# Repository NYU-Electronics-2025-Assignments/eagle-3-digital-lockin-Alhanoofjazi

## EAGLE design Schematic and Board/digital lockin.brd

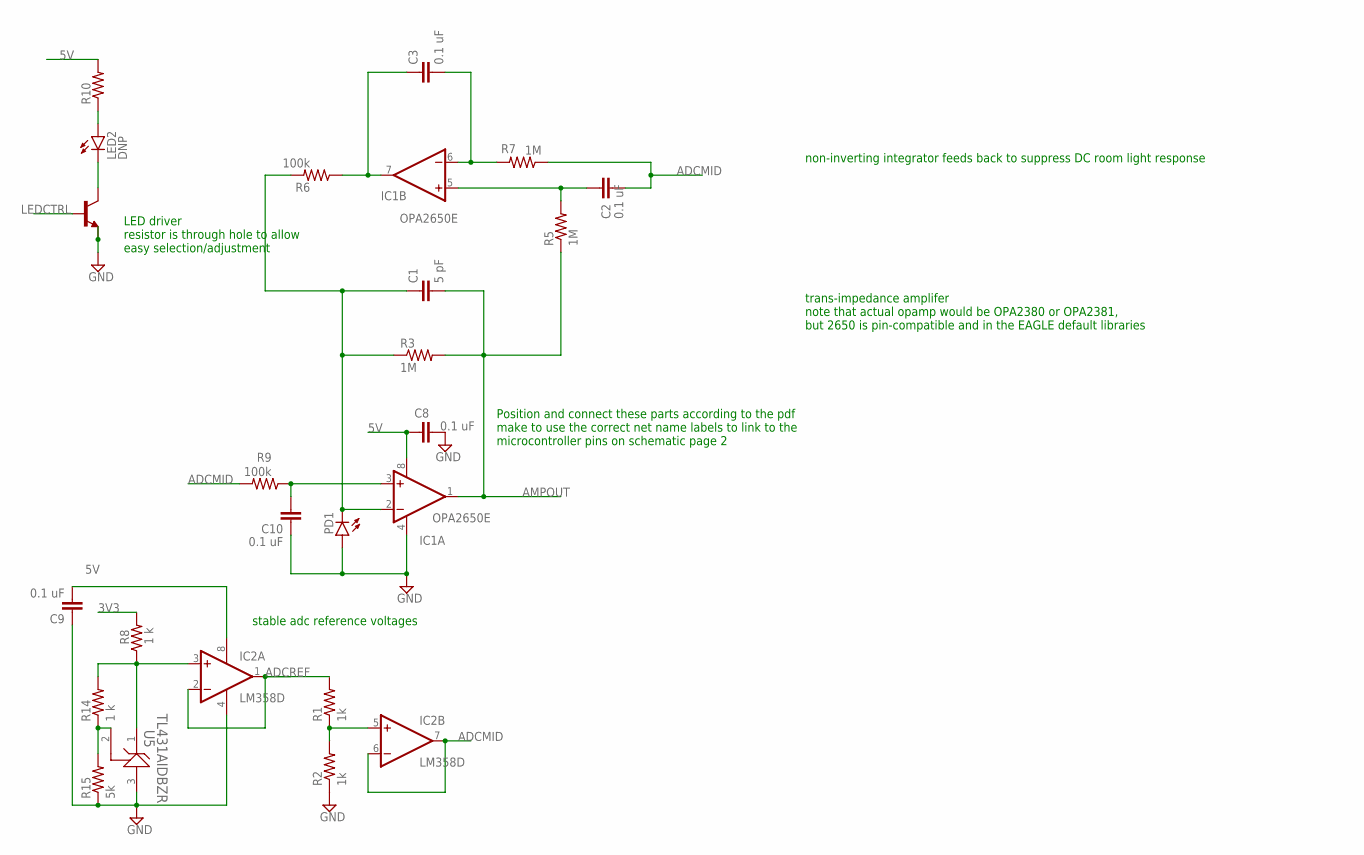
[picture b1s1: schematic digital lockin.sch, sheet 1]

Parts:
C1: 5 pF; C0805
C2, C3, C8, C9, C10: 0.1 uF; C0805; LCSC_PART# C28233
IC1: OPA2650E; MSOP08; LCSC_PART# C181662
IC2: LM358D; SO08; LCSC_PART# C7950
LED2: DNP; LED5MM
PD1: DNP; LED5MM
R1, R2: 1k; R0805; LCSC_PART# C17513
R3, R5, R7: 1M; R0805; LCSC_PART# C17514
R6, R9: 100k; R0805; LCSC_PART# C149504
R8, R14: 1 k; R0805; LCSC_PART# C17513
R10: DNP; 0204V
R15: 5k; R0805
T2: NPN; SOT23-BEC; LCSC_PART# C2145
U5: TL431AIDBZR; DBZ0003A_N; LCSC_PART# C3113

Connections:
3V3: R8.2; also elsewhere on the board
5V: C9.2, IC2.8 (V+), R10.2; also elsewhere on the board
ADCMID: IC2.6 (-IN), IC2.7 (OUT); also elsewhere on the board
ADCREF: IC2.1 (OUT), IC2.2 (-IN), R1.2; also elsewhere on the board
GND: C8.2, C9.1, C10.1, IC1.4 (V-), IC2.4 (V-), PD1.A, R2.1, R15.1, T2.E, U5.3 (ANODE); also elsewhere on the board
LEDCTRL: T2.B; also elsewhere on the board
unnamed: C2.1, IC1.5 (+IN), R5.2
unnamed: C1.1, IC1.2 (-IN), PD1.K (C), R3.1, R6.2
unnamed: LED2.K (C), T2.C
unnamed: C2.2, R7.1
unnamed: C3.2, IC1.6 (-IN), R7.2
unnamed: C3.1, IC1.7 (OUT), R6.1
unnamed: C1.2, IC1.1 (OUT), R3.2, R5.1
unnamed: C8.1, IC1.8 (V+)
unnamed: IC2.3 (+IN), R8.1, R14.2, U5.1 (CATHODE)
unnamed: IC2.5 (+IN), R1.1, R2.2
unnamed: LED2.A, R10.1
unnamed: C10.2, IC1.3 (+IN), R9.1
unnamed: R14.1, R15.2, U5.2 (REF)

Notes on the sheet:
non-inverting integrator feeds back to suppress DC room light response
trans-impedance amplifer note that actual opamp would be OPA2380 or OPA2381, but 2650 is pin-compatible and in the EAGLE default libraries
LED driver resistor is through hole to allow easy selection/adjustment
stable adc reference voltages
Position and connect these parts according to the pdf make to use the correct net name labels to link to the microcontroller pins on schematic page 2
ADCMID
AMPOUT

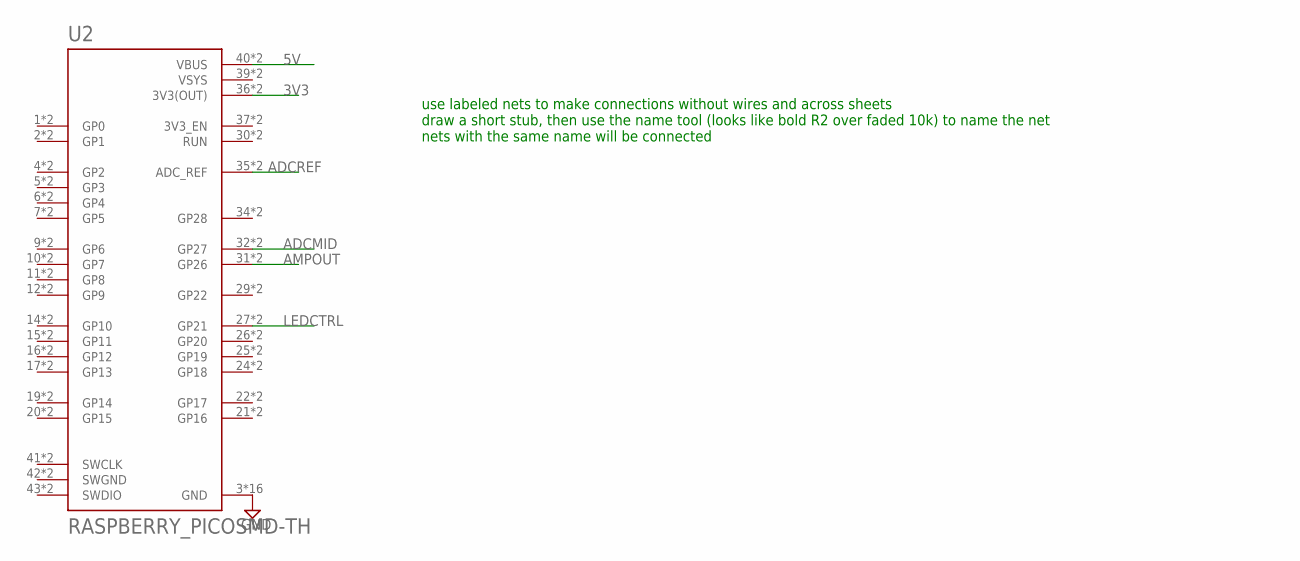
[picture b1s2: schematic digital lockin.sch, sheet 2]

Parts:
U2: RASPBERRY_PICOSMD-TH; PICO-PKG

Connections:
3V3: U2.36 (3V3(OUT)), U2.P$36 (3V3(OUT)); also elsewhere on the board
5V: U2.40 (VBUS), U2.P$40 (VBUS); also elsewhere on the board
ADCMID: U2.32 (GP27), U2.P$32 (GP27); also elsewhere on the board
ADCREF: U2.35 (ADC_REF), U2.P$35 (ADC_REF); also elsewhere on the board
AMPOUT: U2.31 (GP26), U2.P$31 (GP26)
GND: U2.3 (GND), U2.8 (GND), U2.13 (GND), U2.18 (GND), U2.23 (GND), U2.28 (GND), U2.33 (GND), U2.38 (GND), U2.P$3 (GND), U2.P$8 (GND), U2.P$13 (GND), U2.P$18 (GND), U2.P$23 (GND), U2.P$28 (GND), U2.P$33 (GND), U2.P$38 (GND); also elsewhere on the board
LEDCTRL: U2.27 (GP21), U2.P$27 (GP21); also elsewhere on the board
SWGND: U2.42 (SWGND), U2.P$42 (SWGND)
VSYS: U2.39 (VSYS), U2.P$39 (VSYS)

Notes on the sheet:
use labeled nets to make connections without wires and across sheets draw a short stub, then use the name tool (looks like bold R2 over faded 10k) to name the net nets with the same name will be connected

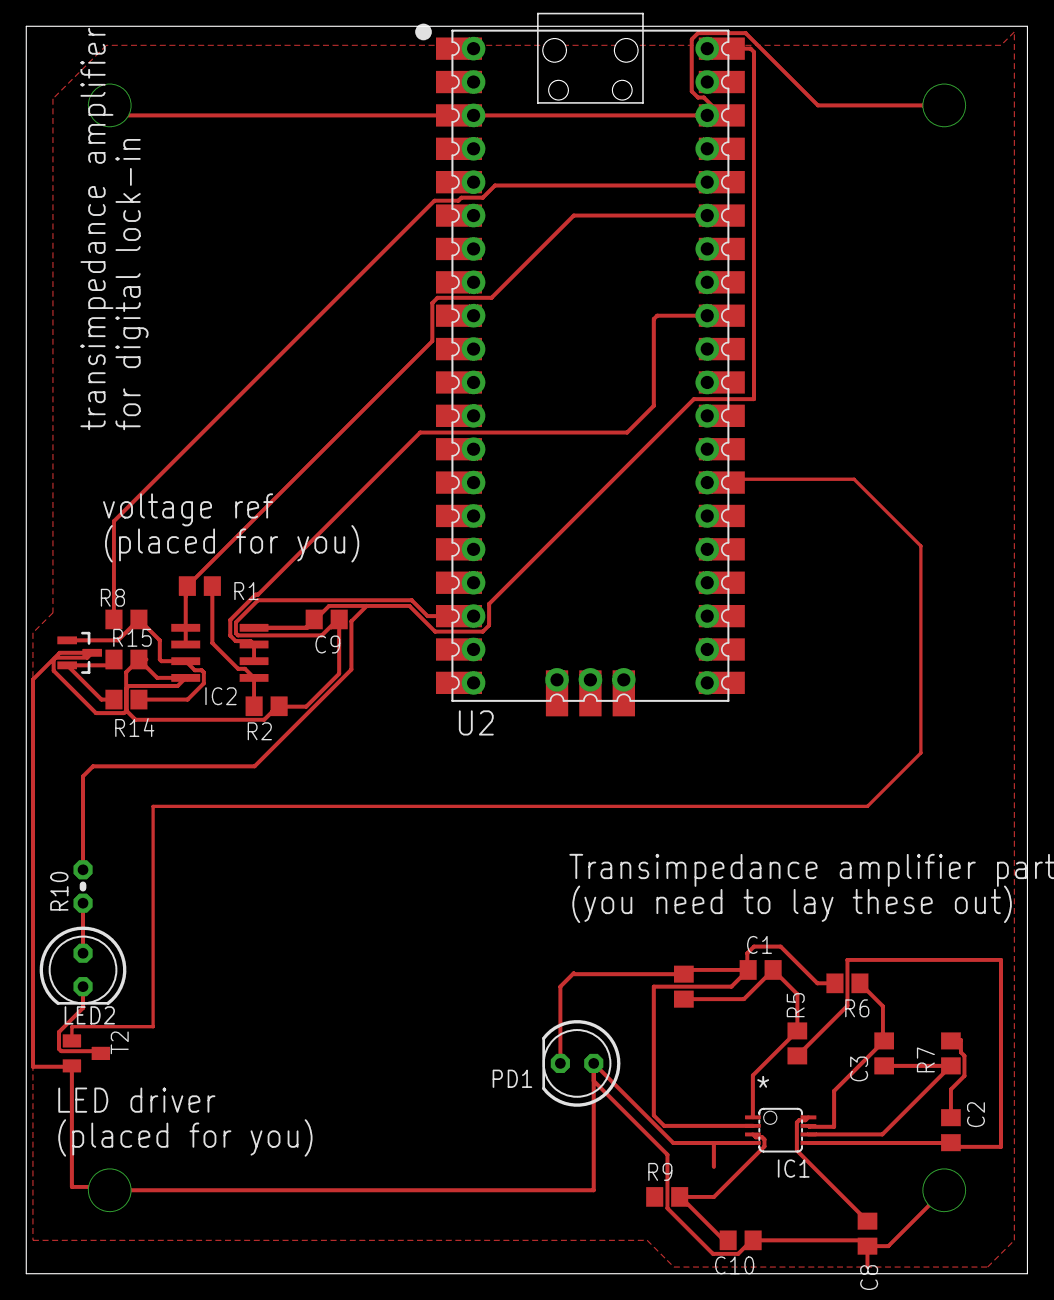
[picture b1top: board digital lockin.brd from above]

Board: 2 copper layers, 76.2 x 94.9 mm, 24 parts (0 on the bottom side), 22 nets.

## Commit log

2025-04-12 add deadline
2025-04-12 Error
    I could not figure out what is causing the overlap error in my brd file.

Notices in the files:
parts and their libraries:
COPYRIGHT: Copyright (C) 2025 Ultra Librarian. All rights reserved.
